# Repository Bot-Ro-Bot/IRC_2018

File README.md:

# IRC_2018
This repo contains the codes, circuits and pcbs and also the documentation for the manual bot built to participate in the International Robotics Challange(IRC) in 2018 at TechFest held by IIT Bombay
.

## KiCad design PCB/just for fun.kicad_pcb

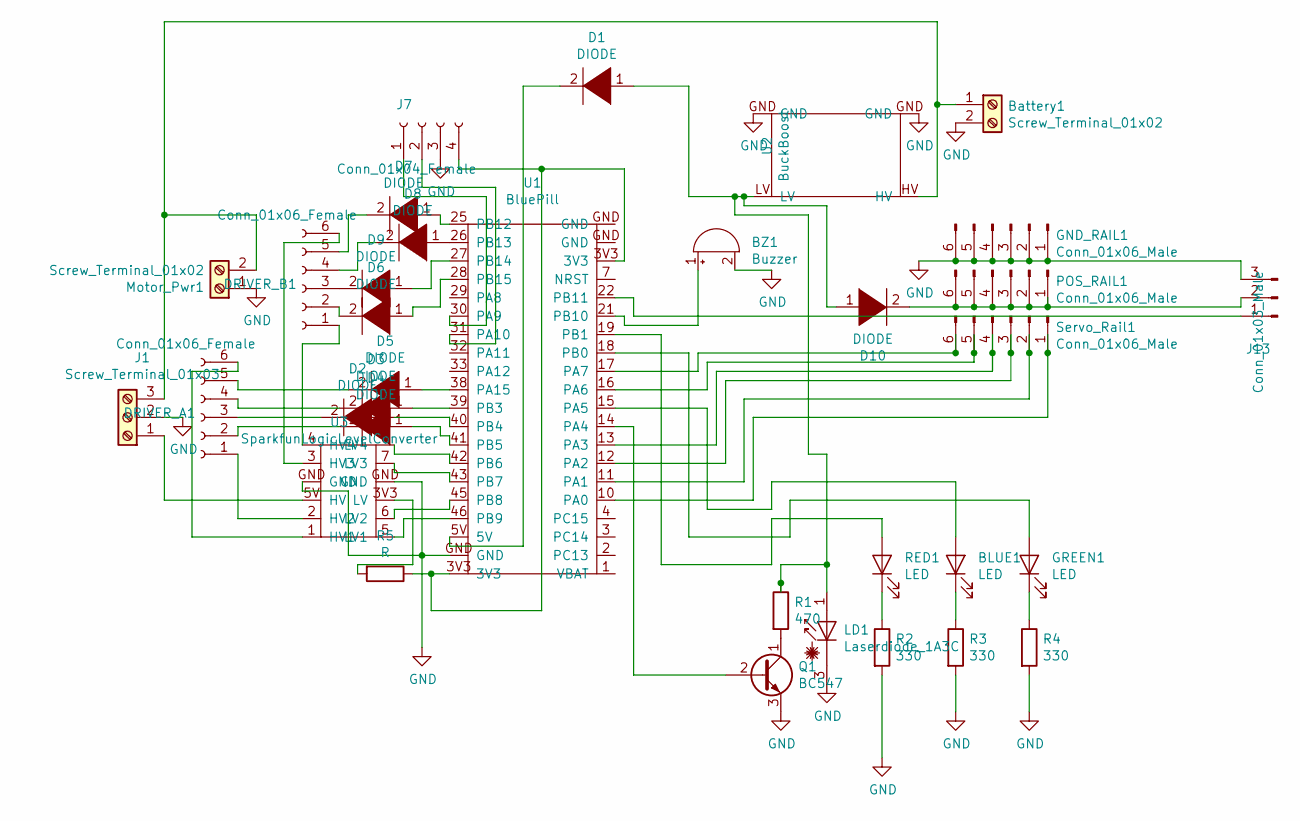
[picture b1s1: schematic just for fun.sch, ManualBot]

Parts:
BLUE1: LED; LED_D5.0mm
BZ1: Buzzer; Buzzer_12x9.5RM7.6
Battery1: Screw_Terminal_01x02; TerminalBlock_MetzConnect_Type094_RT03502HBLU_1x02_P5.00mm_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
D1, D2, D3, D4, D5, D6, D7, D8, D9, D10: DIODE; D_DO-15_P12.70mm_Horizontal
DRIVER_A1: Conn_01x06_Female; L298N
DRIVER_B1: Conn_01x06_Female; L298N
GND_RAIL1: Conn_01x06_Male; PinHeader_1x06_P2.54mm_Horizontal
GREEN1: LED; LED_D5.0mm
J1: Screw_Terminal_01x03; TerminalBlock_MetzConnect_Type094_RT03503HBLU_1x03_P5.00mm_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
J7: Conn_01x04_Female; PinHeader_1x04_P2.54mm_Horizontal
J13: Conn_01x03_Male; PinHeader_1x03_P2.54mm_Horizontal
LD1: Laserdiode_1A3C; LASER
Motor_Pwr1: Screw_Terminal_01x02; TerminalBlock_MetzConnect_Type094_RT03502HBLU_1x02_P5.00mm_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
POS_RAIL1: Conn_01x06_Male; PinHeader_1x06_P2.54mm_Horizontal
Q1: BC547; TO-92_Inline
R1: 470; R_Axial_DIN0207_L6.3mm_D2.5mm_P7.62mm_Horizontal
R2, R3, R4: 330; R_Axial_DIN0207_L6.3mm_D2.5mm_P7.62mm_Horizontal
R5: R; R_Axial_DIN0207_L6.3mm_D2.5mm_P7.62mm_Horizontal
RED1: LED; LED_D5.0mm
Servo_Rail1: Conn_01x06_Male; PinHeader_1x06_P2.54mm_Horizontal
U1: BluePill; STM32BluePill
U2: BuckBoost; BuckBoostConverter(5A)
U3: SparkfunLogicLevelConverter; Logic_level

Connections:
GND: BZ1.2 (+), Battery1.2, GND_RAIL1.1, GND_RAIL1.2, GND_RAIL1.3, GND_RAIL1.4, GND_RAIL1.5, GND_RAIL1.6, J1.2, J7.3, J13.3, LD1.3 (K), Motor_Pwr1.1, Q1.3 (E), R2.2, R3.2, R4.2, U1.GND, U2.GND, U3.GND
unnamed: BLUE1.1 (K), R3.1
unnamed: BLUE1.2 (A), U1.15 (PA5)
unnamed: BZ1.1 (-), U1.21 (PB10)
unnamed: Battery1.1, J1.3, Motor_Pwr1.2, U2.HV
unnamed: D1.1 (K), D10.1 (K), LD1.1 (A), R1.1, U2.LV
unnamed: D1.2 (A), U1.5V
unnamed: D2.1 (K), U1.40 (PB4)
unnamed: D2.2 (A), DRIVER_A1.3
unnamed: D3.1 (K), U1.39 (PB3)
unnamed: D3.2 (A), DRIVER_A1.4
unnamed: D4.1 (K), U1.41 (PB5)
unnamed: D4.2 (A), DRIVER_A1.2
unnamed: D5.1 (K), U1.38 (PA15)
unnamed: D5.2 (A), DRIVER_A1.5
unnamed: D6.1 (K), U1.28 (PB15)
unnamed: D6.2 (A), DRIVER_B1.2
unnamed: D7.1 (K), U1.25 (PB12)
unnamed: D7.2 (A), DRIVER_B1.5
unnamed: D8.1 (K), U1.26 (PB13)
unnamed: D8.2 (A), DRIVER_B1.4
unnamed: D9.1 (K), U1.27 (PB14)
unnamed: D9.2 (A), DRIVER_B1.3
unnamed: D10.2 (A), J13.2, POS_RAIL1.1, POS_RAIL1.2, POS_RAIL1.3, POS_RAIL1.4, POS_RAIL1.5, POS_RAIL1.6
unnamed: DRIVER_A1.1, U3.2 (HV2)
unnamed: DRIVER_A1.6, U3.1 (HV1)
unnamed: DRIVER_B1.1, U3.4 (HV4)
unnamed: DRIVER_B1.6, U3.3 (HV3)
unnamed: GREEN1.1 (K), R4.1
unnamed: GREEN1.2 (A), U1.18 (PB0)
unnamed: J1.1, U3.5V (HV)
unnamed: J7.1, U1.30 (PA9)
unnamed: J7.2, U1.31 (PA10)
unnamed: J7.4, R5.1, U1.3V3
unnamed: J13.1, U1.22 (PB11)
unnamed: Q1.1 (C), R1.2
unnamed: Q1.2 (B), U1.14 (PA4)
unnamed: R2.1, RED1.1 (K)
unnamed: R5.2, U3.3V3 (LV)
unnamed: RED1.2 (A), U1.19 (PB1)
unnamed: Servo_Rail1.1, U1.10 (PA0)
unnamed: Servo_Rail1.2, U1.11 (PA1)
unnamed: Servo_Rail1.3, U1.12 (PA2)
unnamed: Servo_Rail1.4, U1.13 (PA3)
unnamed: Servo_Rail1.5, U1.16 (PA6)
unnamed: Servo_Rail1.6, U1.17 (PA7)
unnamed: U1.42 (PB6), U3.8 (LV4)
unnamed: U1.43 (PB7), U3.7 (LV3)
unnamed: U1.45 (PB8), U3.6 (LV2)
unnamed: U1.46 (PB9), U3.5 (LV1)

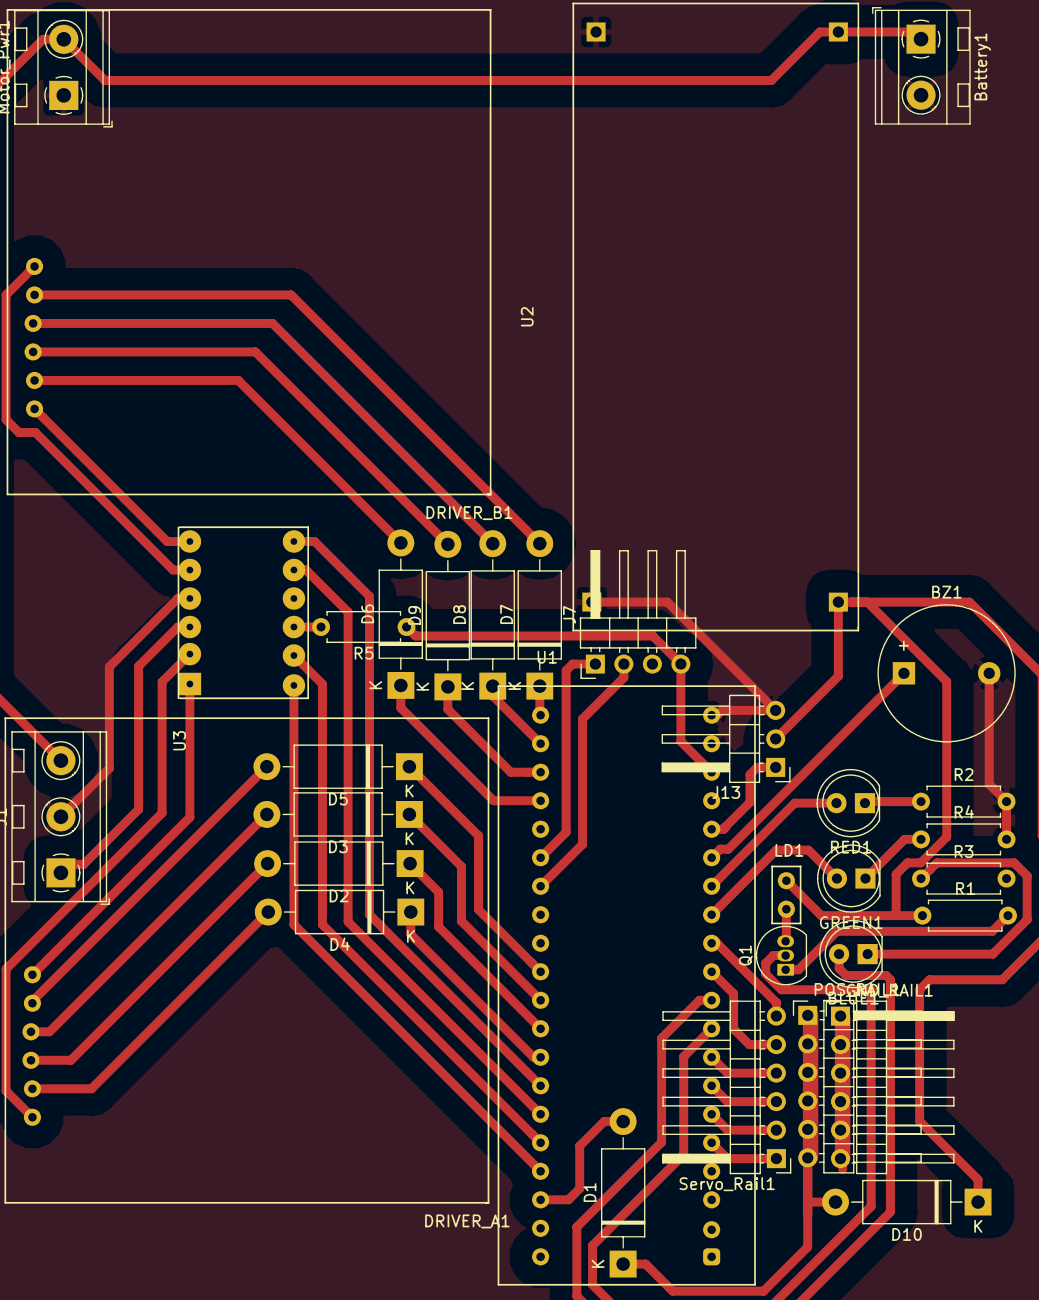
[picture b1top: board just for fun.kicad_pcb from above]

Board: 2 copper layers, 34 parts (0 on the bottom side), 50 nets.

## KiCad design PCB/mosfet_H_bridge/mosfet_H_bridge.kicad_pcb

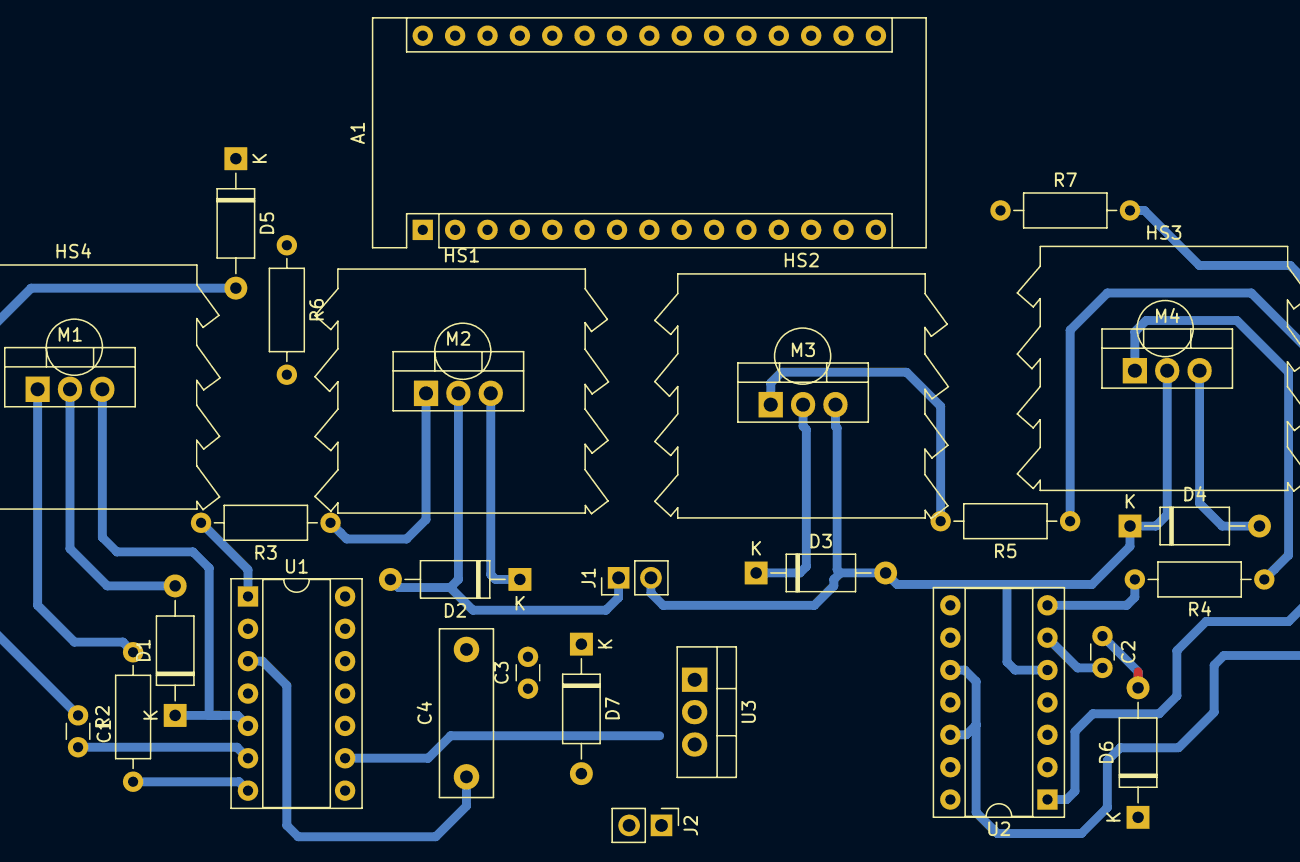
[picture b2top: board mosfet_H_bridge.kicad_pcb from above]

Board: 2 copper layers, 31 parts (0 on the bottom side), 25 nets.

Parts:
A1: Arduino_Nano_v3.x; Arduino_Nano
C1, C2: 1nF; C_Disc_D3.0mm_W1.6mm_P2.50mm
C3: 100nF; C_Disc_D3.0mm_W1.6mm_P2.50mm
C4: 100uF; C_Rect_L13.0mm_W4.0mm_P10.00mm_FKS3_FKP3_MKS4
D1, D2, D3, D4, D5, D6, D7: DIODE; D_A-405_P10.16mm_Horizontal
HS1, HS2, HS3, HS4: Heatsink; Heatsink_Aavid-TV5G_TO220_Horizontal
J1, J2: Conn_01x02_Female; PinHeader_1x02_P2.54mm_Vertical
M1, M2, M3, M4: IRF3205; TO-220-3_Vertical
R2, R3, R4, R5: 330k; R_Axial_DIN0207_L6.3mm_D2.5mm_P10.16mm_Horizontal
R6, R7: 1k; R_Axial_DIN0207_L6.3mm_D2.5mm_P10.16mm_Horizontal
U1, U2: IR2110; DIP-14_W7.62mm_Socket
U3: LM1084-5.0; TO-220-3_Vertical

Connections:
Earth: A1.4, A1.29, C3.2, C4.2, D5.1, D6.1, D7.1, J2.1, U1.11, U1.13, U2.11, U2.13, U3.1
unnamed: A1.5, R6.1
unnamed: A1.11, R7.1
unnamed: C1.1, D5.2
unnamed: C1.2, U1.6
unnamed: C2.1, D6.2
unnamed: C2.2, U2.6
unnamed: C3.1, C4.1, D7.2, J2.2, U1.3, U3.3
unnamed: D1.1, D2.2, J1.1, M1.3, M2.2, U1.5
unnamed: D1.2, M1.2
unnamed: D2.1, M2.3
unnamed: D3.1, M3.2
unnamed: D3.2, D4.1, J1.2, M3.3, M4.2, U2.5
unnamed: D4.2, M4.3
unnamed: M1.1, R2.2
unnamed: M2.1, R3.1
unnamed: M3.1, R5.2
unnamed: M4.1, R4.1
unnamed: R2.1, U1.7
unnamed: R3.2, U1.1
unnamed: R4.2, U2.7
unnamed: R5.1, U2.1
unnamed: R6.2, U1.10, U1.12
unnamed: R7.2, U2.10, U2.12
unnamed: U1.9, U2.9, U3.2

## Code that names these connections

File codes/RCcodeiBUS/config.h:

#ifndef config_h
#define config_h
/*
  PWM PINS         ::    PA8 PA9 PA10 PB6 PB7 PB8 PB9 PB1 PB0 PA7 PA6 PA3 PA2 PA1 PA0
  DIGITAL PINS     ::    PB12 PB13 PB14 PB15 PA11 PA12 PA15 PB3 PB4 PB5 PB11 PB10 PA5 PA4
  ANALOG PINS      ::    PA0 PA1 PA2 PA3 PA4 PA5 PA6 PA7 PB0 PB1
  5V TOLERANT PINS ::
*/



#define BASE 0
#define ARM 1
#define WRIST 2
#define GRIP 3
#define SHOOT 4
#define TILT 5

#define shootPulse 1000

#define RED PB14
#define GREEN PB15
#define BLUE PA8

#define rxPIN PA3

#define laserPin PA15
#define tiltMotor PA6
#define shootMotor PA0


#define rMotorEnable PB1
#define rMotorForward PB10
#define rMotorBack PB11

#define lMotorEnable PB0
#define lMotorForward PB12
#define lMotorBack PB13

#define basePin PB6
#define gripPin PB7
#define wristPin PB8
#define armPin PB9



#endif

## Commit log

2020-05-06 Important Previous Versions
2020-05-07 Added PPM code and iBUS template
2021-05-20 rearranged structure
2021-05-20 updated documentation
